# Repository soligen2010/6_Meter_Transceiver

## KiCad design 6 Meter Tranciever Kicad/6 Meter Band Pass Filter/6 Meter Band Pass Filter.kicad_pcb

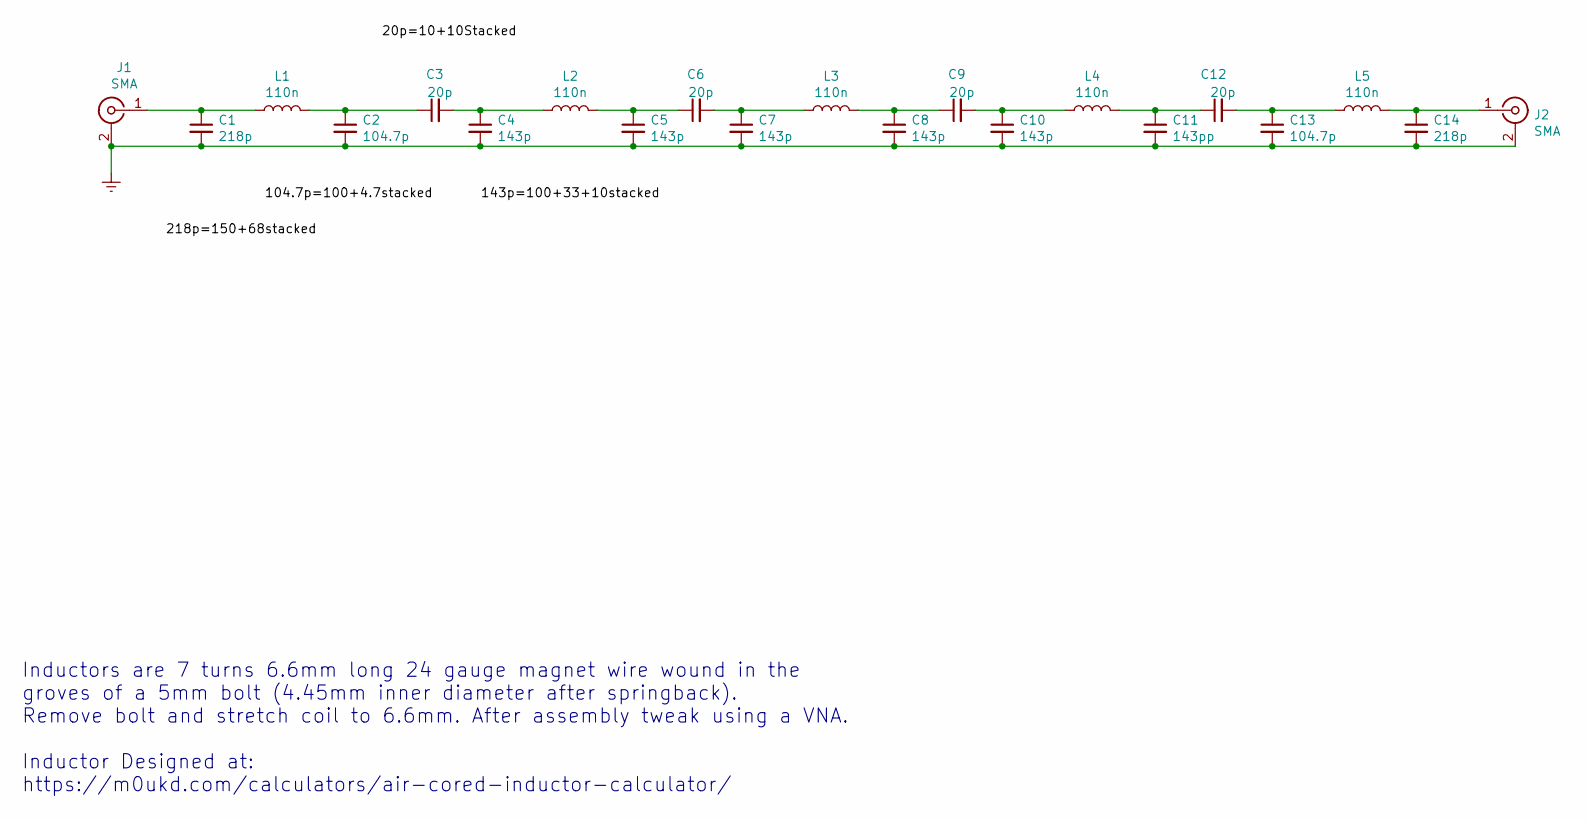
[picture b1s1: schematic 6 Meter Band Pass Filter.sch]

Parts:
C1, C14: 218p; SMD_Combo_1206_0805
C2, C13: 104.7p; SMD_Combo_1206_0805
C3, C6, C9, C12: 20p; SMD_Combo_1206_0805
C4, C5, C7, C8, C10: 143p; SMD_Combo_1206_0805
C11: 143pp; SMD_Combo_1206_0805
J1, J2: SMA; SMA_Molex_73251-2120_EdgeMount_Horizontal
L1, L2, L3, L4, L5: 110n; L_Axial_L5.3mm_D2.2mm_P7.62mm_Horizontal_Vishay_IM-1

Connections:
GNDREF: C1.2, C2.2, C4.2, C5.2, C7.2, C8.2, C10.2, C11.2, C13.2, C14.2, J1.2 (Ext), J2.2 (Ext)
unnamed: C1.1, J1.1 (In), L1.1
unnamed: C2.1, C3.1, L1.2
unnamed: C3.2, C4.1, L2.1
unnamed: C5.1, C6.1, L2.2
unnamed: C6.2, C7.1, L3.1
unnamed: C8.1, C9.1, L3.2
unnamed: C9.2, C10.1, L4.1
unnamed: C11.1, C12.1, L4.2
unnamed: C12.2, C13.1, L5.1
unnamed: C14.1, J2.1 (In), L5.2

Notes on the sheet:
Inductors are 7 turns 6.6mm long 24 gauge magnet wire wound in the groves of a 5mm bolt (4.45mm inner diameter after springback). Remove bolt and stretch coil to 6.6mm. After assembly tweak using a VNA. Inductor Designed at: https://m0ukd.com/calculators/air-cored-inductor-calculator/

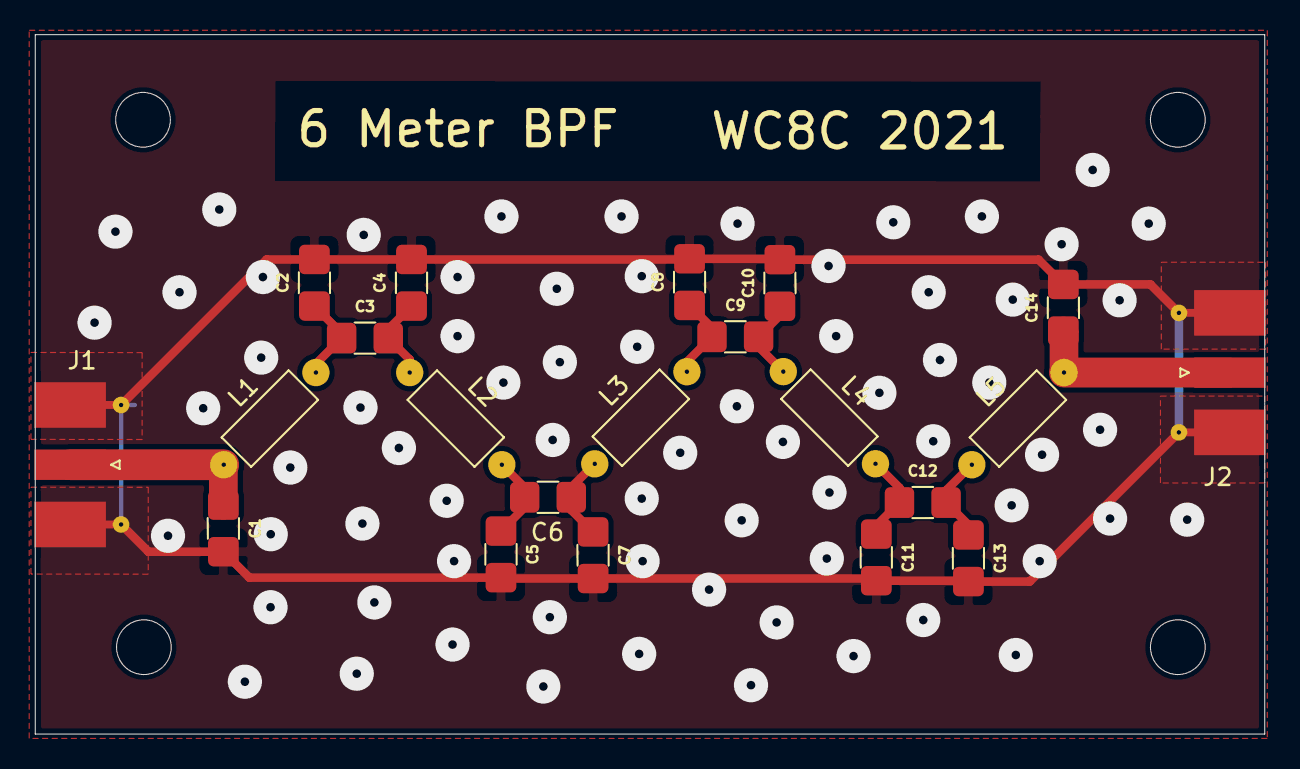
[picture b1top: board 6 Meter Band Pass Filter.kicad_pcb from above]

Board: 2 copper layers, 71.9 x 40.9 mm, 25 parts (0 on the bottom side), 11 nets.

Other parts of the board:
 : MountingHole_3.2mm_M3
 #2,  #3,  #4: MountingHole_3.2mm_M3

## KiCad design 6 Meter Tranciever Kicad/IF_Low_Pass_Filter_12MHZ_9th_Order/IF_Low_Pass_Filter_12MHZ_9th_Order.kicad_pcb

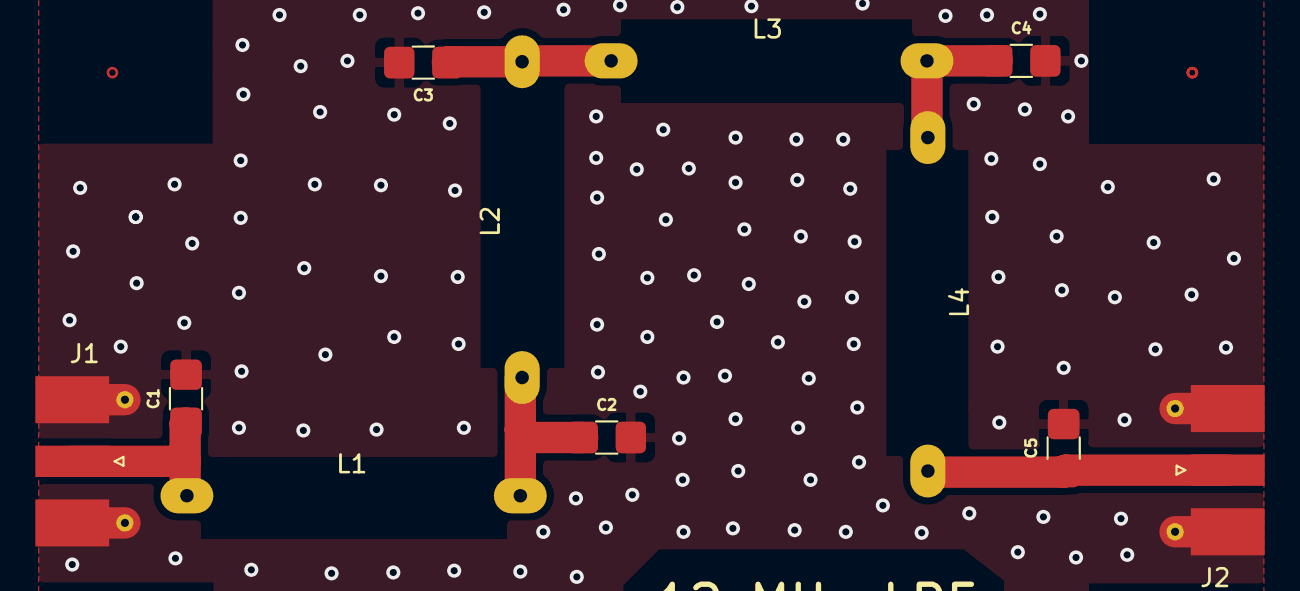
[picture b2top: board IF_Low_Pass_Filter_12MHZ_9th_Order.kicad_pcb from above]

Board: 2 copper layers, 11 parts (0 on the bottom side), 6 nets.

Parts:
C1, C5: 300p; SMD_Combo_1206_0805
C2, C4: 544p7; SMD_Combo_1206_0805
C3: 560p; SMD_Combo_1206_0805
J1, J2: SMA; SMA_Molex_73251-2120_EdgeMount_Horizontal
L1, L4: 909n; 18.9mm_Inductor
L2, L3: 1050n; 17.9mm_Inductor

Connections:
GNDREF: C1.2, C2.2, C3.2, C4.2, C5.2, J1.2, J2.2
unnamed: C1.1, J1.1, L1.1
unnamed: C2.1, L1.2, L2.1
unnamed: C3.1, L2.2, L3.1
unnamed: C4.1, L3.2, L4.1
unnamed: C5.1, J2.1, L4.2
